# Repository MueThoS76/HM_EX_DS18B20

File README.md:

# HM_EX_DS18B20

Bestelliste:
https://www.develektro.com/index.php?wlid=d17e31c0754e7b7b550573e62defc361&jtl=w

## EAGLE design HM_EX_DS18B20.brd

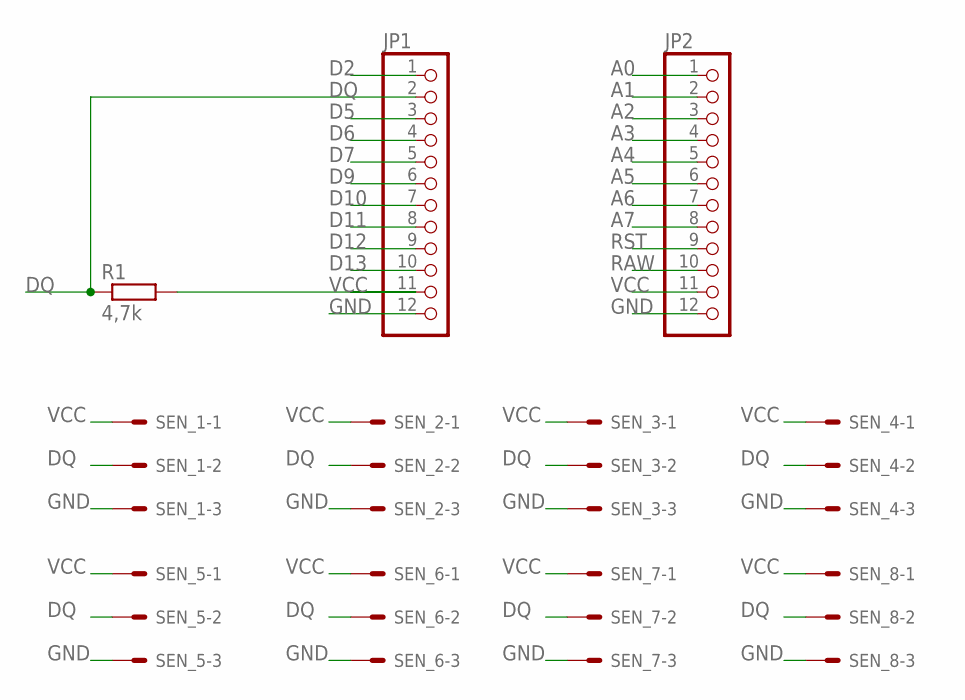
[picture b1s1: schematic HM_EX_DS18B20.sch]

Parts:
JP1, JP2: PINHD-1X12; 1X12
R1: 4,7k; 0207/10
SEN_1, SEN_2, SEN_3, SEN_4, SEN_5, SEN_6, SEN_7, SEN_8: 22-27-2031-03; 6410-03

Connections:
A0: JP2.1
A1: JP2.2
A2: JP2.3
A3: JP2.4
A4: JP2.5
A5: JP2.6
A6: JP2.7
A7: JP2.8
D2: JP1.1
D5: JP1.3
D6: JP1.4
D7: JP1.5
D9: JP1.6
D10: JP1.7
D11: JP1.8
D12: JP1.9
D13: JP1.10
DQ: JP1.2, R1.1, SEN_1.2, SEN_2.2, SEN_3.2, SEN_4.2, SEN_5.2, SEN_6.2, SEN_7.2, SEN_8.2
GND: JP1.12, JP2.12, SEN_1.3, SEN_2.3, SEN_3.3, SEN_4.3, SEN_5.3, SEN_6.3, SEN_7.3, SEN_8.3
RAW: JP2.10
RST: JP2.9
VCC: JP1.11, JP2.11, R1.2, SEN_1.1, SEN_2.1, SEN_3.1, SEN_4.1, SEN_5.1, SEN_6.1, SEN_7.1, SEN_8.1

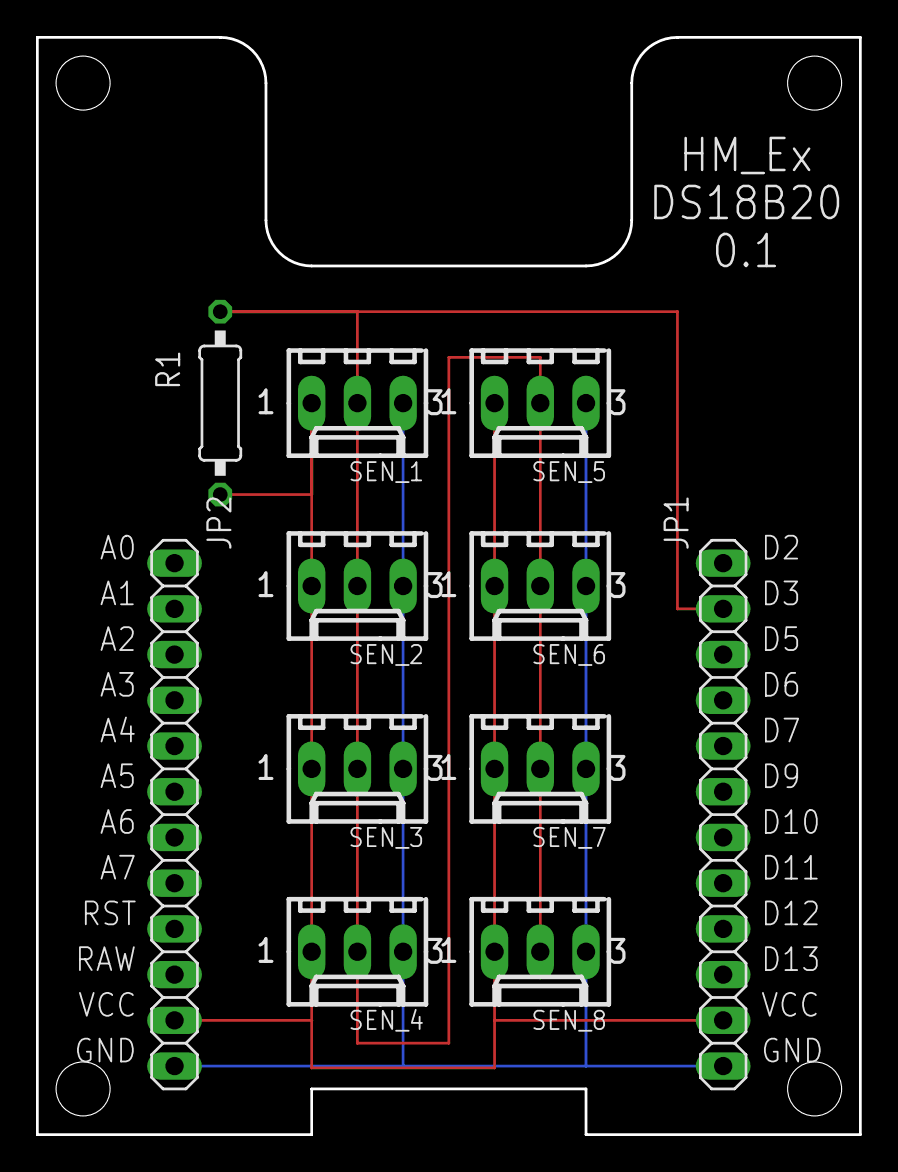
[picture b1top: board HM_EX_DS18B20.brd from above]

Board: 2 copper layers, 45.7 x 61.0 mm, 11 parts (0 on the bottom side), 3 nets.

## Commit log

2019-01-04 Anpassungen
    Bild hunzugefügt und Layout angepasst
